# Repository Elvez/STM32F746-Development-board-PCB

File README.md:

# STM32F746-Development-board-PCB
Development board for the STM32F746VGT6 with micro SD card slot.

I used KiCAD for the project, here are some images of the PCB.

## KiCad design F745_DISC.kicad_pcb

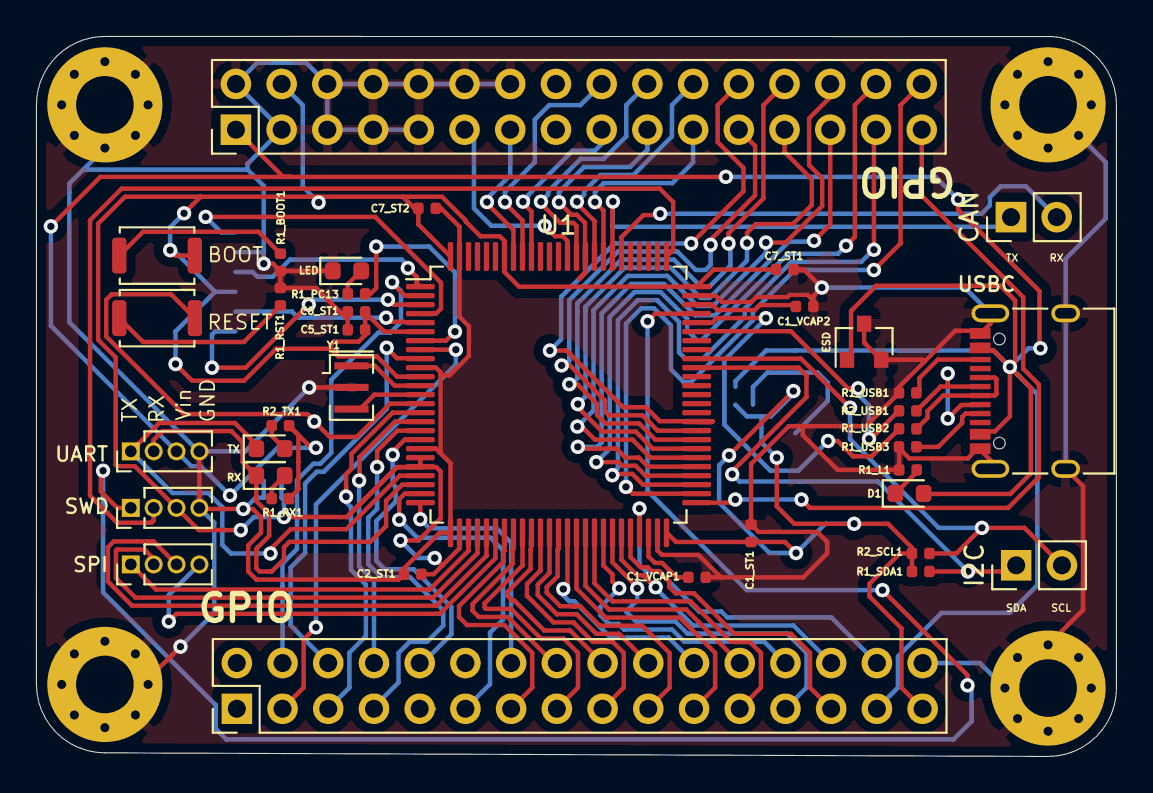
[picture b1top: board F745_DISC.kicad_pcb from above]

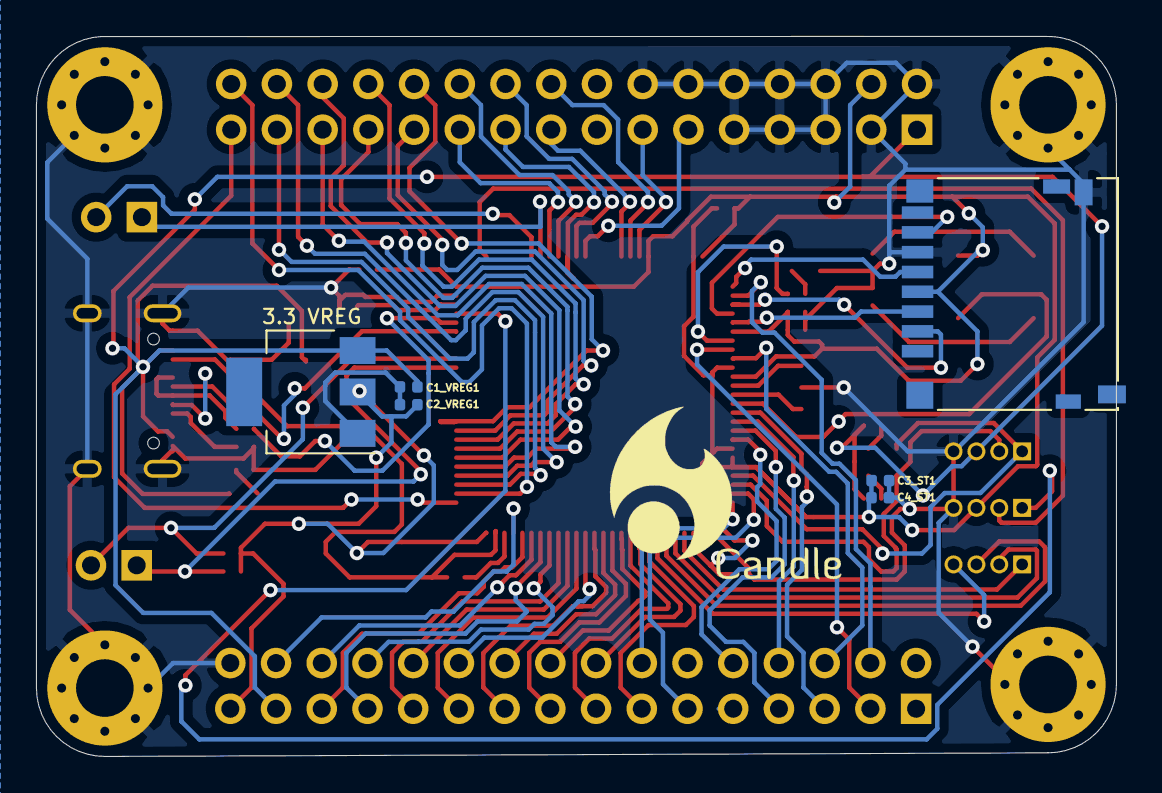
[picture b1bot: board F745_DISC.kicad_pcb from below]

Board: 2 copper layers, 60.0 x 40.0 mm, 48 parts (6 on the bottom side), 80 nets.

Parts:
3.3 VREG: NCP1117-3.3_SOT223; SOT-223-3_TabPin2
 : imageee
BOOT: SW_DIP_x01; SW_Push_SPST_NO_Alps_SKRK
C1_ST1, C2_ST1, C3_ST1, C4_ST1, C5_ST1, C6_ST1, C7_ST2: 100n; C_0402_1005Metric
C1_VCAP1, C1_VCAP2: 4.7u; C_0402_1005Metric
C1_VREG1, C2_VREG1: 10u; C_0402_1005Metric
C7_ST1: 1u; C_0402_1005Metric
CAN: Conn_01x02; PinHeader_1x02_P2.54mm_Vertical
D1: LED; LED_0603_1608Metric
ESD: CM1213A-01SO; SOT-23
H0, H1, H2, H3: MountingHole_Pad; MountingHole_3.2mm_M3_Pad_Via
I2C: Conn_01x02; PinHeader_1x02_P2.54mm_Vertical
J1: Micro_SD_Card; microSD_HC_Hirose_DM3D-SF
J3, J4: Conn_02x16_Odd_Even; PinHeader_2x16_P2.54mm_Vertical
LED: LED; LED_0603_1608Metric
R1_BOOT1, R1_RST1, R1_SDA1, R2_SCL1: 10k; R_0402_1005Metric
R1_L1, R1_PC13, R1_RX1, R2_TX1: 330; R_0402_1005Metric
R1_USB1, R1_USB3: 5.1k; R_0402_1005Metric
R1_USB2, R2_USB1: 22; R_0402_1005Metric
RESET: SW_DIP_x01; SW_Push_SPST_NO_Alps_SKRK
RX: LED; LED_0603_1608Metric
SPI: Conn_01x04; PinHeader_1x04_P1.27mm_Vertical
SWD: Conn_01x04; PinHeader_1x04_P1.27mm_Vertical
TX: LED; LED_0603_1608Metric
U1: STM32F746VGTx; LQFP-100_14x14mm_P0.5mm
UART: Conn_01x04; PinHeader_1x04_P1.27mm_Vertical
USBC: USB_C_Receptacle; USB_C_Receptacle_XKB_U262-16XN-4BVC11
Y1: 16Mhz; Resonator_SMD_muRata_CSTxExxV-3Pin_3.0x1.1mm

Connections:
5V_IN: 3.3 VREG.3, C1_VREG1.1, D1.2, ESD.1, J3.1, J4.29, R1_RX1.2, R2_TX1.2, UART.3, USBC.A4, USBC.A9, USBC.B4, USBC.B9
BOOT: 3.3 VREG.2, BOOT.1, C1_ST1.2, C2_ST1.2, C2_VREG1.2, C3_ST1.2, C4_ST1.2, C5_ST1.2, C6_ST1.2, C7_ST1.2, C7_ST2.2, J1.4, J3.4, J4.31, R1_SDA1.2, R2_SCL1.1, SWD.3, U1.6, U1.11, U1.20, U1.21, U1.27, U1.50, U1.75, U1.94, U1.100
CAN_RX: CAN.2, U1.81
CAN_TX: CAN.1, U1.82
GND: 3.3 VREG.1, C1_ST1.1, C1_VCAP1.2, C1_VCAP2.1, C1_VREG1.2, C2_ST1.1, C2_VREG1.1, C3_ST1.1, C4_ST1.1, C5_ST1.1, C6_ST1.1, C7_ST1.1, C7_ST2.1, ESD.2, ESD.3, H0.1, H1.1, H2.1, H3.1, J1.6, J1.9, J3.2, J3.3, J3.5, J3.6, J3.7, J3.8, J3.9, J3.10, J3.12, J3.14, J4.32, LED.1, R1_BOOT1.1, R1_L1.1, R1_RST1.1, R1_USB1.1, R1_USB3.1, SWD.4, U1.10, U1.19, U1.26, U1.49, U1.74, U1.99, UART.4, USBC.A1, USBC.A12, USBC.B1, USBC.B12, USBC.S1, Y1.2
LED: R1_PC13.2, U1.7
MISO: SPI.3, U1.30
MISO1: J1.7, U1.4
MOSI: SPI.4, U1.31
MOSI1: J1.3, U1.5
NRST: RESET.1, U1.14
NSS: SPI.1, U1.28
NSS1: J1.2, U1.3
unnamed: BOOT.2, R1_BOOT1.2
unnamed: R1_RST1.2, RESET.2
unnamed: D1.1, R1_L1.2
unnamed: R1_RX1.1, RX.2
unnamed: R2_TX1.1, TX.2
unnamed: LED.2, R1_PC13.1
unnamed: R1_USB3.2, USBC.A5
unnamed: R1_USB2.1, USBC.A6, USBC.B6
unnamed: R2_USB1.1, USBC.A7, USBC.B7
unnamed: R1_USB1.2, USBC.B5
OSC_IN: U1.12, Y1.1
OSC_OUT: U1.13, Y1.3
PA2: J4.11, U1.24
PA3: J4.14, U1.25
PB0: J4.15, U1.34
PB1: J4.18, U1.35
PB2: J4.17, U1.36
PB5: J3.17, U1.91
PB10: J4.27, U1.46
PB11: J4.30, U1.47
PB12: J3.31, U1.51
PB13: J3.32, U1.52
PB14: J3.29, U1.53
PB15: J3.30, U1.54
PC0: J4.5, U1.15
PC1: J4.8, U1.16
PC2: J4.7, U1.17
PC3: J4.10, U1.18
PC4: J4.13, U1.32
PC5: J4.16, U1.33
PC9: J3.18, U1.92
PC11: J3.13, U1.93
PC14: J4.3, U1.8
PC15: J4.6, U1.9
PD2: J3.21, U1.83
PD3: J3.22, U1.84
PD4: J3.19, U1.85
PD5: J3.20, U1.86
PD6: J3.11, U1.87
PD8: J3.27, U1.55
PD9: J3.28, U1.56
PD10: J3.25, U1.57
PD11: J3.26, U1.58
PD12: J3.23, U1.59
PD13: J3.24, U1.60
PE3: J4.4, U1.2
PE7: J4.20, U1.37
PE8: J4.19, U1.38
PE9: J4.22, U1.39
PE10: J4.21, U1.40
PE11: J4.24, U1.41
PE12: J4.23, U1.42
PE13: J4.26, U1.43
PE14: J4.25, U1.44
PE15: J4.28, U1.45
RX: RX.1, U1.23, UART.2
SCK: SPI.2, U1.29
SCK1: J1.5, U1.1
SCL: I2C.2, R2_SCL1.2, U1.67
SDA: I2C.1, R1_SDA1.1, U1.66
SWCLK: SWD.2, U1.76
SWDIO: SWD.1, U1.72
TX: TX.1, U1.22, UART.1
USB_DM: R2_USB1.2, U1.70
USB_DP: R1_USB2.2, U1.71
VCAP_1: C1_VCAP1.1, U1.48
VCAP_2: C1_VCAP2.2, U1.73
